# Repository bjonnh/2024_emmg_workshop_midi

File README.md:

Work in progress

More explanations here: https://www.bjonnh.net/project/emmg_midi_synth_controller/

Inspired by:
https://github.com/todbot/eight_by
https://github.com/todbot/picoslidertoy
https://github.com/todbot/pico_test_synth

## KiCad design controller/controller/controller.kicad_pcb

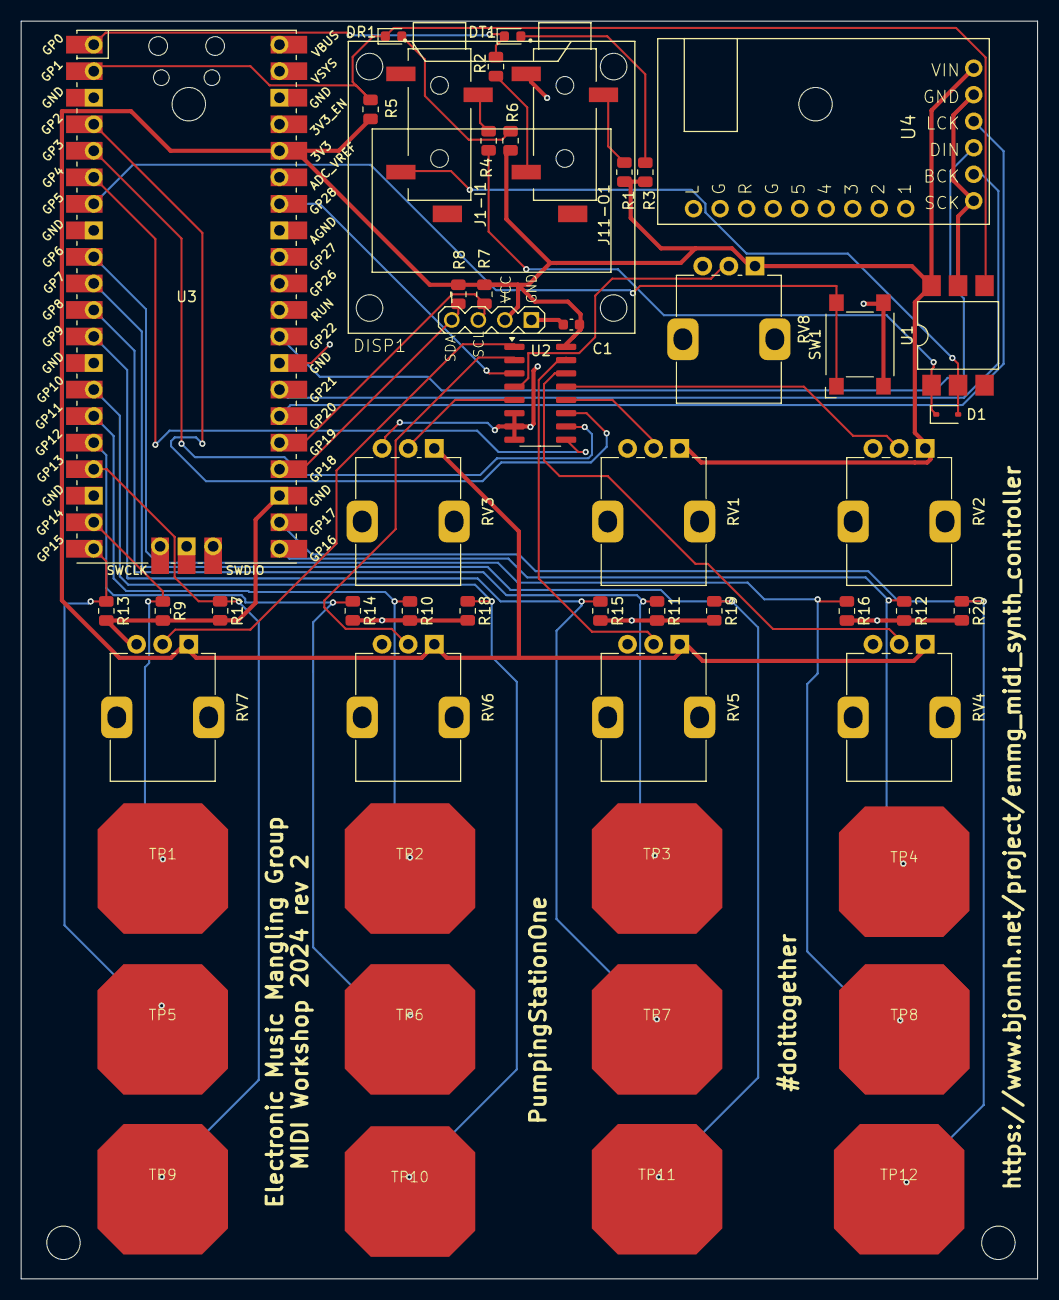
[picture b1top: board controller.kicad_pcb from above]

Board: 2 copper layers, 97.3 x 120.4 mm, 56 parts (0 on the bottom side), 35 nets.

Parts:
C1: 100n; C_0603_1608Metric
D1: 1N4148WS; D_SOD-323
DISP1: DISPLAY-OLED-128X64-I2CTOD; DISPLAY-OLED-128X64-I2C-TOD
DR1: LED; LED_0603_1608Metric
DT1: LED; LED_0603_1608Metric
Hole1, Hole2, Hole3: MountingHole_3.2mm_M3
Hole4: MountingHoles are 3.2mm_M3; MountingHole_3.2mm_M3
J1-I1, J11-O1: SJ-3524-SMT; CUI_SJ-3524-SMT
R1: 33; R_0805_2012Metric
R2: 10; R_0805_2012Metric
R3, R6: 2.2K; R_0805_2012Metric
R4: 220; R_0805_2012Metric
R5: 470; R_0805_2012Metric
R7, R8: 4.7k; R_0805_2012Metric
R9, R10, R11, R12, R13, R14, R15, R16, R17, R18, R19, R20: 1M; R_0805_2012Metric
RV1, RV2, RV3, RV4, RV5, RV6, RV7, RV8: 10K; Potentiometer_Alps_RK09K_Single_Vertical
SW1: SW_Omron_B3FS; SW_SPST_Omron_B3FS-101xP
TP1, TP2, TP3, TP4, TP5, TP6, TP7, TP8, TP9, TP10, TP11, TP12: TOUCHPADA; PAD_Touch_bjo
U1: H11L1; SMDIP-6_W9.53mm
U2: 74HC4051; SOIC-16_3.9x9.9mm_P1.27mm
U3: Pico; RPi_Pico_SMD_TH
U4: I2S_PCM_51XX_SOUNDCARD; I2S_PCM_5100_SOUNDCARD

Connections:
+3V3: C1.1, DISP1.2 (VCC), R1.1, R3.1, R5.2, R6.1, R7.1, R8.1, RV1.1, RV2.1, RV3.1, RV4.1, RV5.1, RV6.1, RV7.1, RV8.1, U1.6, U2.16 (VCC), U3.36 (3V3), U4.VIN
/AIN: U2.3 (A), U3.34 (GPIO28_ADC2)
/AS0: U2.11 (S0), U3.4 (GPIO2)
/AS1: U2.10 (S1), U3.5 (GPIO3)
/AS2: U2.9 (S2), U3.6 (GPIO4)
/I2S_BCK: U3.27 (GPIO21), U4.BCK
/I2S_DATA: U3.29 (GPIO22), U4.DIN
/I2S_LRCK: U3.26 (GPIO20), U4.LCK
/MIDI input 1/RX: DR1.1 (K), R5.1, U1.4, U3.2 (GPIO1)
/Midi Output 1/TX: DT1.1 (K), R2.1, U3.1 (GPIO0)
/POT1: RV1.2, U2.12 (A3)
/POT2: RV2.2, U2.13 (A0)
/POT3: RV3.2, U2.5 (A5)
/POT4: RV4.2, U2.14 (A1)
/POT5: RV5.2, U2.15 (A2)
/POT6: RV6.2, U2.2 (A6)
/POT7: RV7.2, U2.1 (A4)
/POT8: RV8.2, U2.4 (A7)
/SCL: DISP1.3 (SCL), R7.2, U3.25 (GPIO19)
/SDA: DISP1.4 (SDA), R8.2, U3.24 (GPIO18)
/SW: SW1.1, U3.7 (GPIO5)
/TPAD1: R9.1, TP1.1 (TOUCH), U3.19 (GPIO14)
/TPAD2: R10.1, TP2.1 (TOUCH), U3.15 (GPIO11)
/TPAD3: R11.1, TP3.1 (TOUCH), U3.11 (GPIO8)
/TPAD4: R12.1, TP4.1 (TOUCH), U3.21 (GPIO16)
/TPAD5: R13.1, TP5.1 (TOUCH), U3.20 (GPIO15)
/TPAD6: R14.1, TP6.1 (TOUCH), U3.16 (GPIO12)
/TPAD7: R15.1, TP7.1 (TOUCH), U3.12 (GPIO9)
/TPAD8: R16.1, TP8.1 (TOUCH), U3.9 (GPIO6)
/TPAD9: R17.1, TP9.1 (TOUCH), U3.17 (GPIO13)
/TPAD10: R18.1, TP10.1 (TOUCH), U3.14 (GPIO10)
/TPAD11: R19.1, TP11.1 (TOUCH), U3.10 (GPIO7)
/TPAD12: R20.1, TP12.1 (TOUCH), U3.22 (GPIO17)
GND: C1.2, DISP1.1 (GND), J11-O1.1, R9.2, R10.2, R11.2, R12.2, R13.2, R14.2, R15.2, R16.2, R17.2, R18.2, R19.2, R20.2, RV1.3, RV2.3, RV3.3, RV4.3, RV5.3, RV6.3, RV7.3, RV8.3, SW1.2, U1.5, U2.6 (~E), U2.7 (VEE), U2.8 (GND), U3.23 (GND), U3.28 (GND), U3.38 (GND), U4.GND, U4.SCK
unnamed: D1.2 (A), J1-I1.2, U1.2

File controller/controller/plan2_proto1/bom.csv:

Comment,Designator,Footprint,Qty,LCSC
100n,C1,Capacitor_SMD:C_0603_1608Metric,1,C14663
1N4148WS,D1,Diode_SMD:D_SOD-323,1,C2128
LED,DR1,LED_SMD:LED_0603_1608Metric,1,C2286 
LED,DT1,LED_SMD:LED_0603_1608Metric,1,C72038
33,R1,Resistor_SMD:R_0805_2012Metric,1,C17634 
10,R2,Resistor_SMD:R_0805_2012Metric,1,C17415 
2.2K,"R3,R6",Resistor_SMD:R_0805_2012Metric,2,C17520
220,R4,Resistor_SMD:R_0805_2012Metric,1,C17557
470,R5,Resistor_SMD:R_0805_2012Metric,1,C17710
4.7k,"R7,R8",Resistor_SMD:R_0805_2012Metric,2,C17673
1M,"R9,R10,R11,R12,R13,R14,R15,R16,R17,R18,R19,R20",Resistor_SMD:R_0805_2012Metric,12,C17514
10K,"RV1,RV2,RV3,RV4,RV5,RV6,RV7,RV8",Plugin,8,C209770
SW_Omron_B3FS,SW1,Button_Switch_SMD:SW_SPST_Omron_B3FS-101xP,1,C2888769
H11L1,U1,Package_DIP:SMDIP-6_W9.53mm,1,C78589
74HC4051,U2,Package_SO:SOIC-16_3.9x9.9mm_P1.27mm,1,C9386

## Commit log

2024-07-12 update to v2
2024-07-13 prototype 1 sent to production
2024-07-14 Mure Stoff
2024-07-19 Weird stuff
2024-07-25 Add last soft version
2024-08-07 current code
2024-08-11 Current
2024-08-27 prototype v2
2024-09-01 Add c++ code
2024-09-06 Better c++ version
2024-09-07 Add PANIC support
2024-09-07 Add persistence of settings and load/save
2024-09-07 Add support for CC and latching CCs on pads
2024-09-08 *10 speed boost, Switch to LittleFS, fix race conditions
2024-09-10 Create LICENSE
2024-09-11 Add synthesizer
2024-09-15 Start moving the synth into a class
2024-09-15 Some more synth integration
2024-09-16 Some more stuff for the synth
2024-09-17 Update display speed and parameters display in synth
2024-09-20 Synth with all pages
2024-09-28 Merged
2024-09-28 Fix path
2024-09-28 Add pages
2024-09-28 Fix stylesheet
2024-10-26 fix knobs noise. start notes at C
2024-10-29 Add presentation for signals and pixels
2025-06-29 Add .gitignore, documentation, MIDI CC mapping, and support for additional MIDI event handling
2025-07-03 Add MIDI-controlled mode and CC update throttling
2025-07-03 Some optimizations for the midi controlled mode
